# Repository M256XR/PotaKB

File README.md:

# PotaKB

XIAO nRF52840ベースのワイヤレスキーボード・マウス複合デバイス。

## 概要

- **MCU**: Seeed XIAO nRF52840
- **キー数**: 65キー（8×8マトリクス × MCP23017 + 直接接続2キー）
- **接続**: Bluetooth LE（3スロット独立切替）/ USB HID
- **スティック**: アナログスティックによるマウス操作・スクロール（EMAスムージング）
- **設定**: Web Configuratorからリアルタイム書き換え（BLE / USB Serial）

## 主な機能

### Bluetooth
- **3スロット独立接続**（PotaKB-1 / PotaKB-2 / PotaKB-3）
  - スロットごとに固有のBLEアドレスとボンドDBを持つ → 同一PCで複数スロット使用可
  - スロット別LEDカラー：BT1=青 / BT2=水色 / BT3=マゼンタ
- **高速通信**: `BANDWIDTH_MAX`（hvn_qsize=3）+ 接続インターバル7.5ms → 約500Hz
- BT中にUSBを刺すと自動でUSBモードに切替

### USB
- HID Resolution Multiplier対応（対応OSで高精度スクロール）
- VID=`0x239A` / PID=`0x8029`

### その他
- 一定時間無操作でLEDオフ（スリープ）、操作で即復帰
- バッテリー残量通知（BLE Battery Service）
- フラッシュへのキーマップ・設定の永続保存

## ディレクトリ構成

```
program/PotaKB_fw/
├── PotaKB_fw.ino          ファームウェア (Arduino / nRF52 core)
├── keymap.h               キーマップ定義・デフォルト設定値
└── PotaKB_Configurator/   Web設定ツール (BLE + USB Serial対応)
    ├── index.html
    ├── style.css
    └── script.js

tools/
├── .arduino-user/         カスタムライブラリ（改造済み Bluefruit52Lib）
├── build.ps1              ビルドスクリプト
├── flash.ps1              フラッシュスクリプト
├── setup.ps1              環境セットアップ
└── arduino-cli.yaml       arduino-cli設定

kicad/                     KiCAD回路図・PCBデータ
stl/                       3Dプリント用STLモデル
SPEC.md                    ファームウェア仕様書
```

## ビルド環境

arduino-cli を使用（Arduino IDE不要）。

### 初回セットアップ

```
tools/1_setup.bat
```

ボードパッケージ（Seeeduino nRF52）と依存ライブラリを自動インストール。

### ビルド・フラッシュ

```
tools/2_build.bat   # コンパイル
tools/3_flash.bat   # USB Serial DFUでフラッシュ
```

### 依存ライブラリ（tools/.arduino-user/libraries に同梱）

- `Bluefruit52Lib`（スロット別ボンドDB対応に改造）
- `Adafruit_MCP23017_Arduino_Library`
- `Adafruit_BusIO`

## Configuratorの使い方

`program/PotaKB_fw/PotaKB_Configurator/index.html` をブラウザ（Chrome / Edge）で開く。

- **Bluetooth接続**: デバイス名 `PotaKB-1` / `PotaKB-2` / `PotaKB-3` で接続
- **USB Serial接続**: VID=`0x239A` / PID=`0x8029` で接続
- キーをクリックして選択し、パレットまたはキー入力で割り当て
- 接続時にバッテリー残量を自動取得

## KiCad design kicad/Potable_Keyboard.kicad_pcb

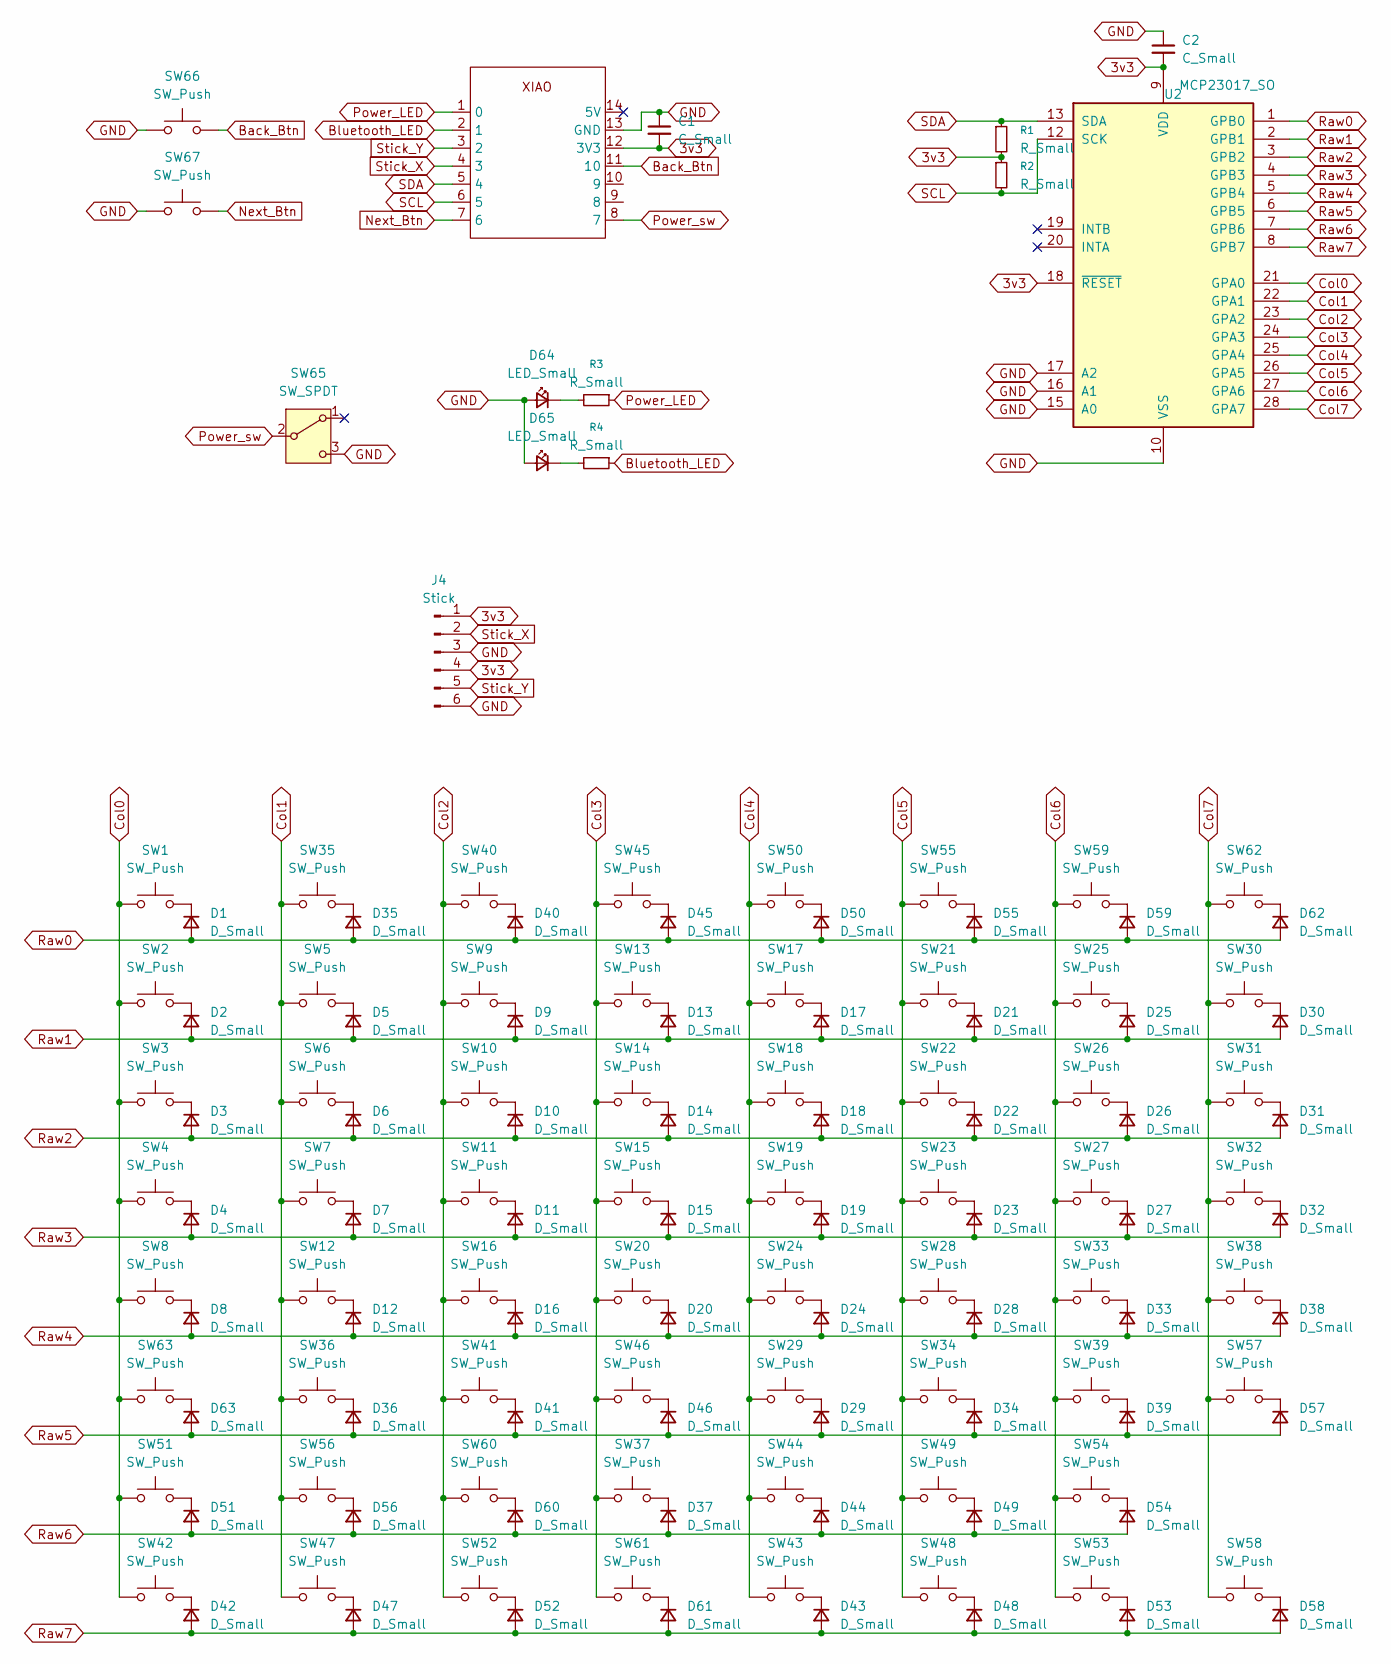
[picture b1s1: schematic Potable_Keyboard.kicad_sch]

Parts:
C1, C2: C_Small; C_0603_1608Metric_Pad1.08x0.95mm_HandSolder
D1, D2, D3, D4, D5, D6, D7, D8, D9, D10, D11, D12, D13, D14, D15, D16, D17, D18, D19, D20, D21, D22, D23, D24, D25, D26, D27, D28, D29, D30, D31, D32, D33, D34, D35, D36, D37, D38, D39, D40, D41, D42, D43, D44, D45, D46, D47, D48, D49, D50, D51, D52, D53, D54, D55, D56, D57, D58, D59, D60, D61, D62, D63: D_Small; D_SOD-323
D64, D65: LED_Small; LED_0805_2012Metric_Pad1.15x1.40mm_HandSolder
J4: Stick; LowHeightJoyStickWithButton
R1, R2, R3, R4: R_Small; R_0603_1608Metric_Pad0.98x0.95mm_HandSolder
SW1, SW62: SW_Push; SW_THBP07-043CW
SW2, SW3, SW4, SW5, SW6, SW7, SW8, SW9, SW10, SW11, SW12, SW13, SW14, SW15, SW16, SW17, SW18, SW19, SW20, SW21, SW22, SW23, SW24, SW25, SW26, SW27, SW28, SW29, SW30, SW31, SW32, SW33, SW34, SW35, SW36, SW37, SW38, SW39, SW40, SW41, SW42, SW43, SW44, SW45, SW46, SW47, SW48, SW49, SW50, SW51, SW52, SW53, SW54, SW55, SW56, SW57, SW58, SW59, SW60, SW61, SW63, SW66, SW67: SW_Push; SW_Tactile_6x6mm_2Pin_P5.0mm
SW65: SW_SPDT; SW_Slide_SPDT_Angled_CK_OS102011MA1Q
U1: Seeeduino XIAO-MOUDLE14P-2.54-21X17.8MM
U2: MCP23017_SO; SSOP-28_5.3x10.2mm_P0.65mm

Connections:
3v3: C1.2, C2.2, J4.1, J4.4, R1.2, R2.1, U1.12 (3V3), U2.9 (VDD), U2.18 (~RESET)
Back_Btn: SW66.2, U1.11 (10)
Bluetooth_LED: R4.1, U1.2 (1)
Col0: SW1.1, SW2.1, SW3.1, SW4.1, SW8.1, SW42.1, SW51.1, SW63.1, U2.21 (GPA0)
Col1: SW5.1, SW6.1, SW7.1, SW12.1, SW35.1, SW36.1, SW47.1, SW56.1, U2.22 (GPA1)
Col2: SW9.1, SW10.1, SW11.1, SW16.1, SW40.1, SW41.1, SW52.1, SW60.1, U2.23 (GPA2)
Col3: SW13.1, SW14.1, SW15.1, SW20.1, SW37.1, SW45.1, SW46.1, SW61.1, U2.24 (GPA3)
Col4: SW17.1, SW18.1, SW19.1, SW24.1, SW29.1, SW43.1, SW44.1, SW50.1, U2.25 (GPA4)
Col5: SW21.1, SW22.1, SW23.1, SW28.1, SW34.1, SW48.1, SW49.1, SW55.1, U2.26 (GPA5)
Col6: SW25.1, SW26.1, SW27.1, SW33.1, SW39.1, SW53.1, SW54.1, SW59.1, U2.27 (GPA6)
Col7: SW30.1, SW31.1, SW32.1, SW38.1, SW57.1, SW58.1, SW62.1, U2.28 (GPA7)
GND: C1.1, C2.1, D64.2 (A), D65.2 (A), J4.3, J4.6, SW65.3 (C), SW66.1, SW67.1, U1.13 (GND), U2.10 (VSS), U2.15 (A0), U2.16 (A1), U2.17 (A2)
unnamed: D1.1 (K), SW1.2
unnamed: D2.1 (K), SW2.2
unnamed: D3.1 (K), SW3.2
unnamed: D4.1 (K), SW4.2
unnamed: D5.1 (K), SW5.2
unnamed: D6.1 (K), SW6.2
unnamed: D7.1 (K), SW7.2
unnamed: D8.1 (K), SW8.2
unnamed: D9.1 (K), SW9.2
unnamed: D10.1 (K), SW10.2
unnamed: D11.1 (K), SW11.2
unnamed: D12.1 (K), SW12.2
unnamed: D13.1 (K), SW13.2
unnamed: D14.1 (K), SW14.2
unnamed: D15.1 (K), SW15.2
unnamed: D16.1 (K), SW16.2
unnamed: D17.1 (K), SW17.2
unnamed: D18.1 (K), SW18.2
unnamed: D19.1 (K), SW19.2
unnamed: D20.1 (K), SW20.2
unnamed: D21.1 (K), SW21.2
unnamed: D22.1 (K), SW22.2
unnamed: D23.1 (K), SW23.2
unnamed: D24.1 (K), SW24.2
unnamed: D25.1 (K), SW25.2
unnamed: D26.1 (K), SW26.2
unnamed: D27.1 (K), SW27.2
unnamed: D28.1 (K), SW28.2
unnamed: D29.1 (K), SW29.2
unnamed: D30.1 (K), SW30.2
unnamed: D31.1 (K), SW31.2
unnamed: D32.1 (K), SW32.2
unnamed: D33.1 (K), SW33.2
unnamed: D34.1 (K), SW34.2
unnamed: D35.1 (K), SW35.2
unnamed: D36.1 (K), SW36.2
unnamed: D37.1 (K), SW37.2
unnamed: D38.1 (K), SW38.2
unnamed: D39.1 (K), SW39.2
unnamed: D40.1 (K), SW40.2
unnamed: D41.1 (K), SW41.2
unnamed: D42.1 (K), SW42.2
unnamed: D43.1 (K), SW43.2
unnamed: D44.1 (K), SW44.2
unnamed: D45.1 (K), SW45.2
unnamed: D46.1 (K), SW46.2
unnamed: D47.1 (K), SW47.2
unnamed: D48.1 (K), SW48.2
unnamed: D49.1 (K), SW49.2
unnamed: D50.1 (K), SW50.2
unnamed: D51.1 (K), SW51.2
unnamed: D52.1 (K), SW52.2
unnamed: D53.1 (K), SW53.2
unnamed: D54.1 (K), SW54.2
unnamed: D55.1 (K), SW55.2
unnamed: D56.1 (K), SW56.2
unnamed: D57.1 (K), SW57.2
unnamed: D58.1 (K), SW58.2
unnamed: D59.1 (K), SW59.2
unnamed: D60.1 (K), SW60.2
unnamed: D61.1 (K), SW61.2
unnamed: D62.1 (K), SW62.2
unnamed: D63.1 (K), SW63.2
unnamed: D64.1 (K), R3.2
unnamed: D65.1 (K), R4.2
Next_Btn: SW67.2, U1.7 (6)
Power_LED: R3.1, U1.1 (0)
Power_sw: SW65.2 (B), U1.8 (7)
Raw0: D1.2 (A), D35.2 (A), D40.2 (A), D45.2 (A), D50.2 (A), D55.2 (A), D59.2 (A), D62.2 (A), U2.1 (GPB0)
Raw1: D2.2 (A), D5.2 (A), D9.2 (A), D13.2 (A), D17.2 (A), D21.2 (A), D25.2 (A), D30.2 (A), U2.2 (GPB1)
Raw2: D3.2 (A), D6.2 (A), D10.2 (A), D14.2 (A), D18.2 (A), D22.2 (A), D26.2 (A), D31.2 (A), U2.3 (GPB2)
Raw3: D4.2 (A), D7.2 (A), D11.2 (A), D15.2 (A), D19.2 (A), D23.2 (A), D27.2 (A), D32.2 (A), U2.4 (GPB3)
Raw4: D8.2 (A), D12.2 (A), D16.2 (A), D20.2 (A), D24.2 (A), D28.2 (A), D33.2 (A), D38.2 (A), U2.5 (GPB4)
Raw5: D29.2 (A), D34.2 (A), D36.2 (A), D39.2 (A), D41.2 (A), D46.2 (A), D57.2 (A), D63.2 (A), U2.6 (GPB5)
Raw6: D37.2 (A), D44.2 (A), D49.2 (A), D51.2 (A), D54.2 (A), D56.2 (A), D60.2 (A), U2.7 (GPB6)
Raw7: D42.2 (A), D43.2 (A), D47.2 (A), D48.2 (A), D52.2 (A), D53.2 (A), D58.2 (A), D61.2 (A), U2.8 (GPB7)
SCL: R2.2, U1.6 (5), U2.12 (SCK)
SDA: R1.1, U1.5 (4), U2.13 (SDA)
Stick_X: J4.2, U1.4 (3)
Stick_Y: J4.5, U1.3 (2)

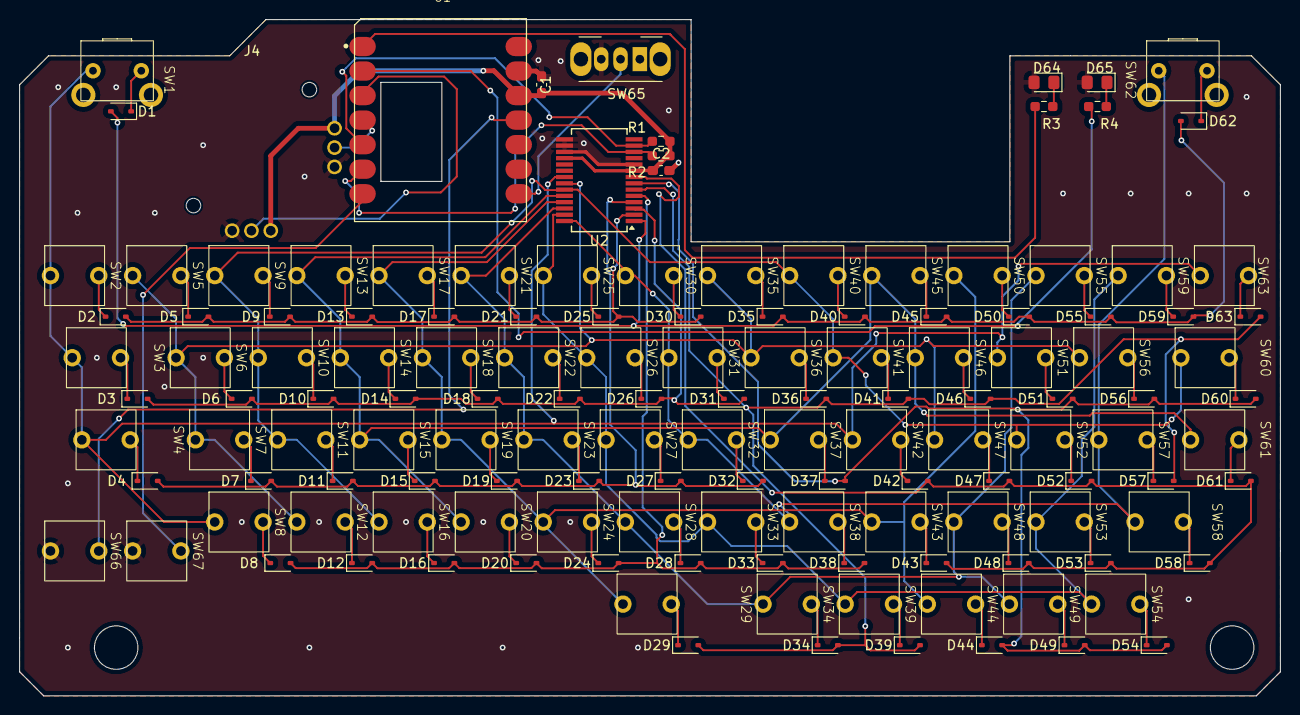
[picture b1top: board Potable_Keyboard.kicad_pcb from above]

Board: 2 copper layers, 130.5 x 70.0 mm, 140 parts (0 on the bottom side), 92 nets.

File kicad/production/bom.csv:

Designator,Footprint,Quantity,Value,LCSC Part #
"C1, C2",0603,2,C_Small,
"D1, D10, D11, D12, D13, D14, D15, D16, D17, D18, D19, D2, D20, D21, D22, D23, D24, D25, D26, D27, D28, D29, D3, D30, D31, D32, D33, D34, D35, D36, D37, D38, D39, D4, D40, D41, D42, D43, D44, D45, D46, D47, D48, D49, D5, D50, D51, D52, D53, D54, D55, D56, D57, D58, D59, D6, D60, D61, D62, D63, D7, D8, D9",D_SOD-323,63,D_Small,
"D64, D65",0805,2,LED_Small,
J4,LowHeightJoyStickWithButton,1,Stick,
"R1, R2, R3, R4",0603,4,R_Small,
"SW1, SW62",SW_THBP07-043CW,2,SW_Push,
"SW10, SW11, SW12, SW13, SW14, SW15, SW16, SW17, SW18, SW19, SW2, SW20, SW21, SW22, SW23, SW24, SW25, SW26, SW27, SW28, SW29, SW3, SW30, SW31, SW32, SW33, SW34, SW35, SW36, SW37, SW38, SW39, SW4, SW40, SW41, SW42, SW43, SW44, SW45, SW46, SW47, SW48, SW49, SW5, SW50, SW51, SW52, SW53, SW54, SW55, SW56, SW57, SW58, SW59, SW6, SW60, SW61, SW63, SW66, SW67, SW7, SW8, SW9",SW_Tactile_6x6mm_2Pin_P5.0mm,63,SW_Push,
SW65,SW_Slide_SPDT_Angled_CK_OS102011MA1Q,1,SW_SPDT,
U1,Seeeduino XIAO-MOUDLE14P-2.54-21X17.8MM,1,~,
U2,SSOP-28_5.3x10.2mm_P0.65mm,1,MCP23017_SO,

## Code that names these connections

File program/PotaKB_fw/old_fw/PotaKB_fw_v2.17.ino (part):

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OperatingMode_t currentMode;

// --- ハードウェアピン定義 ---
#define STICK_X_PIN      A2
#define STICK_Y_PIN      A3
#define BACK_BTN_PIN     D6
#define NEXT_BTN_PIN     D10
#define POWER_SW_PIN     D7
#define POWER_LED_PIN    D0
#define BLUETOOTH_LED_PIN D1
#define BATTERY_PIN      A0

// --- LED制御設定 ---
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  digitalWrite(LED_GREEN, HIGH);
  digitalWrite(LED_BLUE, HIGH);
  
  pinMode(POWER_LED_PIN, OUTPUT);
  analogWrite(POWER_LED_PIN, LED_BRIGHTNESS);
  
  pinMode(BLUETOOTH_LED_PIN, OUTPUT);
  analogWrite(BLUETOOTH_LED_PIN, 0);
  
  pinMode(BACK_BTN_PIN, INPUT_PULLUP);
  pinMode(NEXT_BTN_PIN, INPUT_PULLUP);
  
  // ★★★ 修正点1: 電源スイッチのウェイクアップ設定を反転 ★★★
  pinMode(POWER_SW_PIN, INPUT_PULLUP);
  // HIGHでスリープ、LOWでウェイクアップするように設定
  nrf_gpio_cfg_sense_input(digitalPinToPinName(POWER_SW_PIN), NRF_GPIO_PIN_PULLUP, NRF_GPIO_PIN_SENSE_LOW);

  usb_hid.setPollInterval(2);
  usb_hid.setReportDescriptor(desc_hid_report, sizeof(desc_hid_report));
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// =========================================================================
void loop() {
  // ★★★ 修正点2: スリープに入る条件を反転 ★★★
  if (digitalRead(POWER_SW_PIN) == HIGH) goToSystemOffSleep();

  if (currentMode == MODE_USB && !TinyUSBDevice.mounted()) {
    switchMode(MODE_BLUETOOTH);
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    
    if (isSleeping) {
      setXiaoLed(0, 0, 0);
      analogWrite(BLUETOOTH_LED_PIN, 0);
      if (isAnyActivity()) wakeUpFromSystemOnSleep();
      waitForEvent(); 
    } else {
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          static bool ledState = false;
          ledState = !ledState;
          if (ledState) {
            analogWrite(BLUETOOTH_LED_PIN, LED_BRIGHTNESS);
          } else {
            analogWrite(BLUETOOTH_LED_PIN, 0);
          }
        }
      } else {
        analogWrite(BLUETOOTH_LED_PIN, LED_BRIGHTNESS);
      }
      if (millis() - lastActivityTime > sleepTimeout) goToSystemOnSleep();
    }
  } else {
    setXiaoLed(0, LED_BRIGHTNESS, 0);
    analogWrite(BLUETOOTH_LED_PIN, 0);
  }
}

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    Bluefruit.Advertising.stop();
    
    setXiaoLed(0, LED_BRIGHTNESS, 0);
    analogWrite(BLUETOOTH_LED_PIN, 0);
  } else {
    Bluefruit.Advertising.start(0);
    setXiaoLed(0, 0, LED_BRIGHTNESS);
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
void scanDirectKeys() {
  unsigned long currentTime = millis();
  bool rawBackState = (digitalRead(BACK_BTN_PIN) == LOW);
  if (rawBackState != lastRawBackBtnState) backBtnChangeTime = currentTime;
  lastRawBackBtnState = rawBackState;
  if ((currentTime - backBtnChangeTime) > debounceDelay) backBtnState = rawBackState;
  bool rawNextState = (digitalRead(NEXT_BTN_PIN) == LOW);
  if (rawNextState != lastRawNextBtnState) nextBtnChangeTime = currentTime;
  lastRawNextBtnState = rawNextState;
  if ((currentTime - nextBtnChangeTime) > debounceDelay) nextBtnState = rawNextState;
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  if (millis() - lastMoveTime >= 8) {
    lastMoveTime = millis();
    xTotal -= xReadings[readIndex]; yTotal -= yReadings[readIndex];
    xReadings[readIndex] = analogRead(STICK_Y_PIN); yReadings[readIndex] = analogRead(STICK_X_PIN);
    xTotal += xReadings[readIndex]; yTotal += yReadings[readIndex];
    readIndex = (readIndex + 1) % SMOOTHING_SAMPLES;
    int xAvg = xTotal / SMOOTHING_SAMPLES; int yAvg = yTotal / SMOOTHING_SAMPLES;
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bool isAnyActivity() {
  for (int r = 0; r < ROWS; r++) for (int c = 0; c < COLS; c++) if (keyState[r][c]) return true;
  if (backBtnState || nextBtnState) return true;
  int xVal = analogRead(STICK_Y_PIN);
  int yVal = analogRead(STICK_X_PIN);
  if (abs(xVal - STICK_CENTER_X) > STICK_DEADZONE || abs(yVal - STICK_CENTER_Y) > STICK_DEADZONE) return true;
  return false;
}
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
void goToSystemOffSleep() {
  setXiaoLed(0,0,0);
  analogWrite(BLUETOOTH_LED_PIN, 0);
  analogWrite(POWER_LED_PIN, 0);
  Wire.end();
  NRF_POWER->SYSTEMOFF = 1;
}
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
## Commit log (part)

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2026-03-18 Docs: session01終了処理・セッション管理システム導入・extract_session.pyパス修正
2026-03-18 Docs: session03終了処理・PROGRESS/index/CLAUDE.md更新
2026-03-18 Docs: session05終了処理・PROGRESS/index/CLAUDE.md更新
